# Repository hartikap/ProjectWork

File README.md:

# ProjectWork
Ohjelmistokehitys-koulutuksen projektityö

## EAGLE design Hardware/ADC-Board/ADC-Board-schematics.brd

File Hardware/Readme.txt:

This folder includes all hardware -schematics, layouts and BOMs for different modules of the synthesizer. 
VCO-1, VCA-1 and VCF-1 modules are (for the time being) constructed using the design and instructions 
found from http://www.birthofasynth.com/Thomas_Henry/TH_main.html. Other modules are designed by myself.

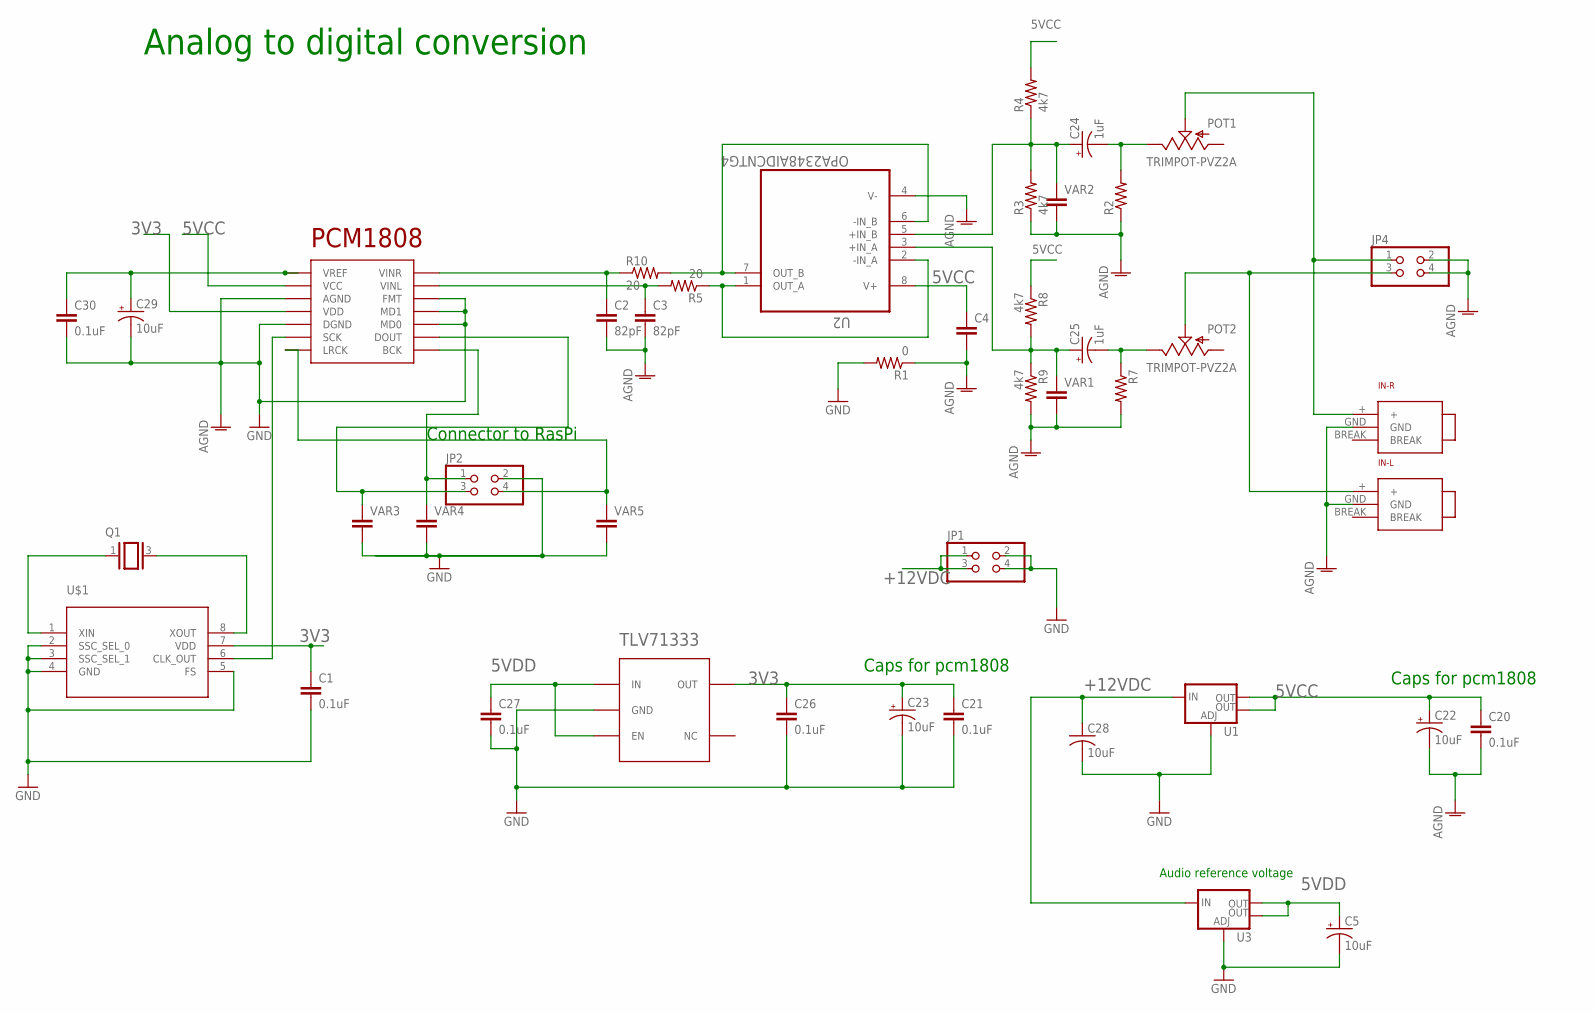
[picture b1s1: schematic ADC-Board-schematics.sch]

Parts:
C1, C20, C21, C26, C27, C30: 0.1uF; C0603
C2, C3: 82pF; 0603-CAP
C4: CAP0603-CAP; 0603-CAP
C5, C22, C23, C29: 10uF; RADIALCAN4MM
C24, C25: 1uF; RADIALCAN4MM
C28: 10uF; C1206
IN-L: 3MM5-PLUG
IN-R: 3MM5-PLUG
JP1, JP2, JP4: PINHD-2X2; 2X02
PCM1808: PCM1808PW; R-PDSO-G14
POT1, POT2: TRIMPOT-PVZ2A; PVZ2A
Q1: XTAL; 5X3CRYSTAL
R1: 0; 0603-RES
R2, R7: RESISTOR0603-RES; 0603-RES
R3, R4, R8, R9: 4k7; 0603-RES
R5, R10: 20; 0603-RES
TLV71333: TVL713; SOT23-5
U1, U3: V_REG_LM1117SOT223; SOT223
U2: OPA2348AIDCNTG4; SOT65P280X145-8N
U$1: CDCS502TSSOP-8; TSSOP-8
VAR1, VAR2, VAR3, VAR4, VAR5: CAP0603-CAP; 0603-CAP

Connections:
3V3: C1.1, C21.1, C23.1 (+), C26.1, PCM1808.4 (VDD), TLV71333.5 (OUT), U$1.7 (VDD)
5VCC: C4.1, C20.1, C22.1 (+), PCM1808.3 (VCC), R4.2, R8.1, U1.2 (OUT), U1.4 (OUT), U2.8 (V+)
5VDD: C5.1 (+), C27.1, TLV71333.1 (IN), TLV71333.3 (EN), U3.2 (OUT), U3.4 (OUT)
+12VDC: C28.1, JP1.1, JP1.3, U1.3 (IN), U3.3 (IN)
AGND: C2.2, C3.2, C4.2, IN-L.GND, IN-R.GND, JP4.2, JP4.4, R1.1, R2.1, R3.1, R7.2, R9.2, U2.4 (V-), VAR1.2, VAR2.2
GND: C1.2, C5.2 (-), C20.2, C21.2, C22.2 (-), C23.2 (-), C26.2, C27.2, C28.2, C29.2 (-), C30.2, JP1.2, JP1.4, JP2.2, PCM1808.2 (AGND), PCM1808.5 (DGND), PCM1808.10 (MD0), PCM1808.11 (MD1), PCM1808.12 (FMT), R1.2, TLV71333.2 (GND), U1.1 (ADJ), U3.1 (ADJ), U$1.2 (SSC_SEL_0), U$1.3 (SSC_SEL_1), U$1.4 (GND), U$1.5 (FS), VAR3.2, VAR4.2, VAR5.2
unnamed: JP2.1, PCM1808.8 (BCK), VAR4.1
unnamed: C24.2 (-), POT1.3 (E), R2.2
unnamed: JP2.3, PCM1808.9 (DOUT), VAR3.1
unnamed: C24.1 (+), R3.2, R4.1, U2.5 (+IN_B), VAR2.1
unnamed: R5.1, U2.1 (OUT_A), U2.2 (-IN_A)
unnamed: C3.1, PCM1808.13 (VINL), R5.2
unnamed: C25.2 (-), POT2.3 (E), R7.1
unnamed: C25.1 (+), R8.2, R9.1, U2.3 (+IN_A), VAR1.1
unnamed: R10.2, U2.6 (-IN_B), U2.7 (OUT_B)
unnamed: C2.1, PCM1808.14 (VINR), R10.1
unnamed: JP2.4, PCM1808.7 (LRCK), VAR5.1
unnamed: IN-L.+, JP4.3, POT2.2 (S)
unnamed: IN-R.+, JP4.1, POT1.2 (S)
unnamed: Q1.1, U$1.1 (XIN)
unnamed: Q1.3 (2), U$1.8 (XOUT)
unnamed: C29.1 (+), C30.1, PCM1808.1 (VREF)
unnamed: PCM1808.6 (SCK), U$1.6 (CLK_OUT)

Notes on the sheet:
Caps for pcm1808
Analog to digital conversion
Connector to RasPi
Audio reference voltage

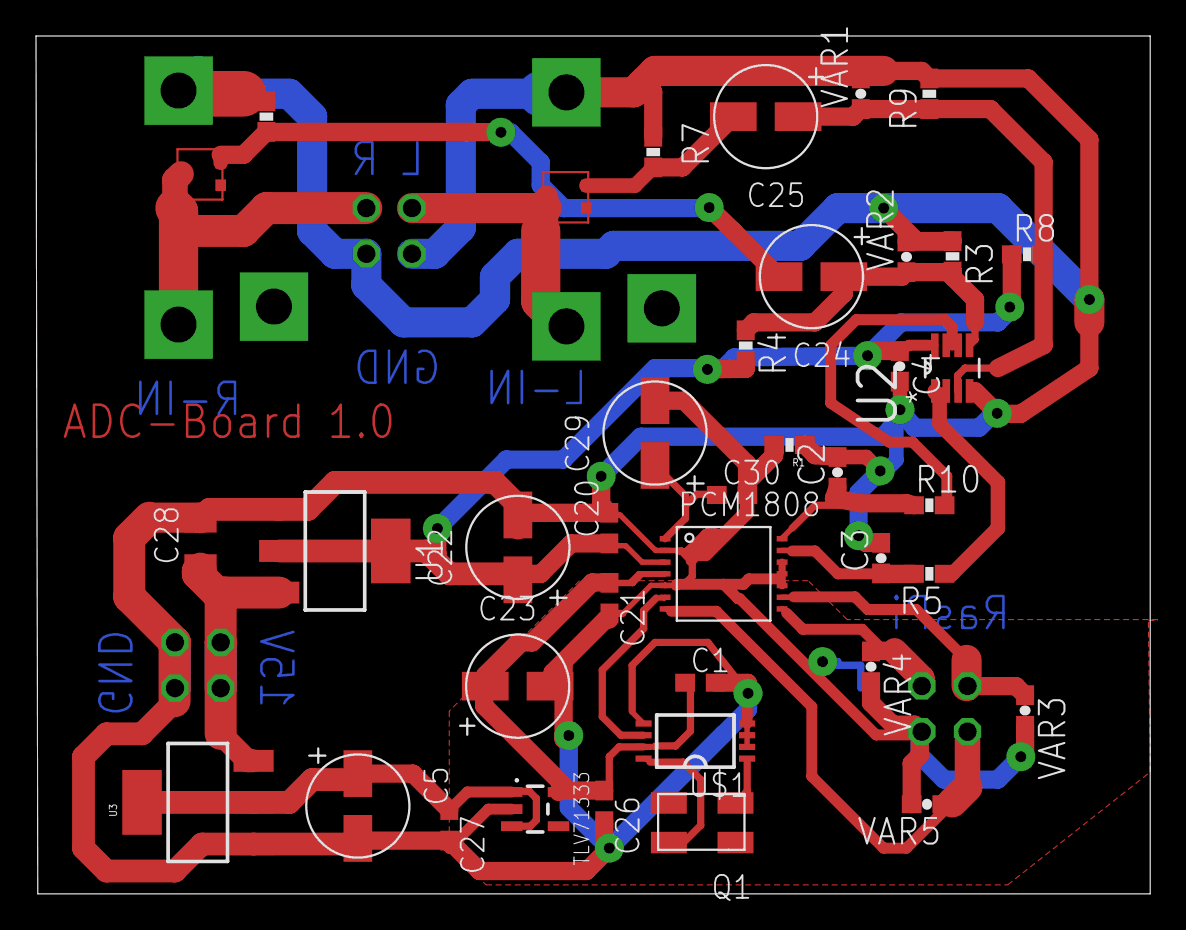
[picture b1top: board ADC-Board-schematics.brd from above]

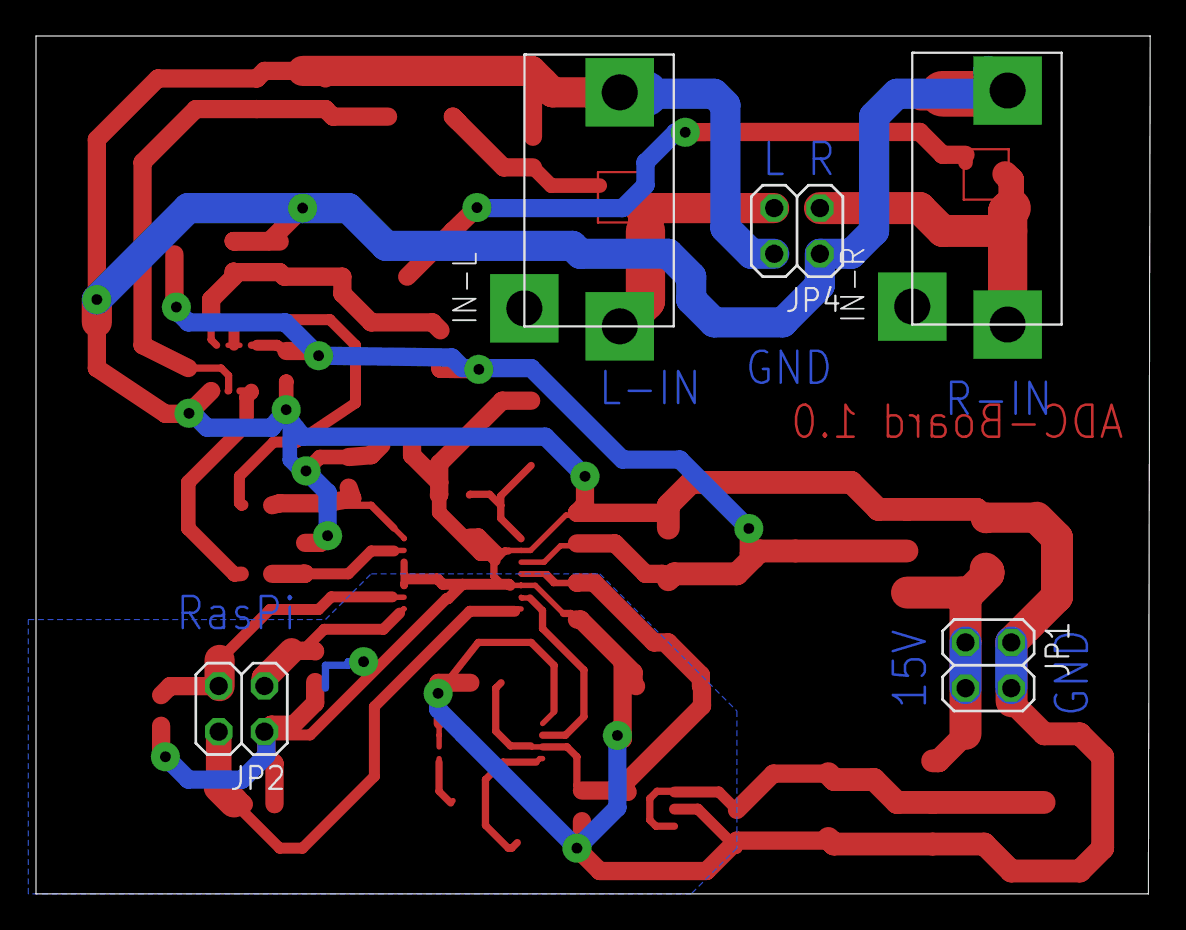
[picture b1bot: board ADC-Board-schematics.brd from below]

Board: 2 copper layers, 61.9 x 47.7 mm, 44 parts (5 on the bottom side), 23 nets.

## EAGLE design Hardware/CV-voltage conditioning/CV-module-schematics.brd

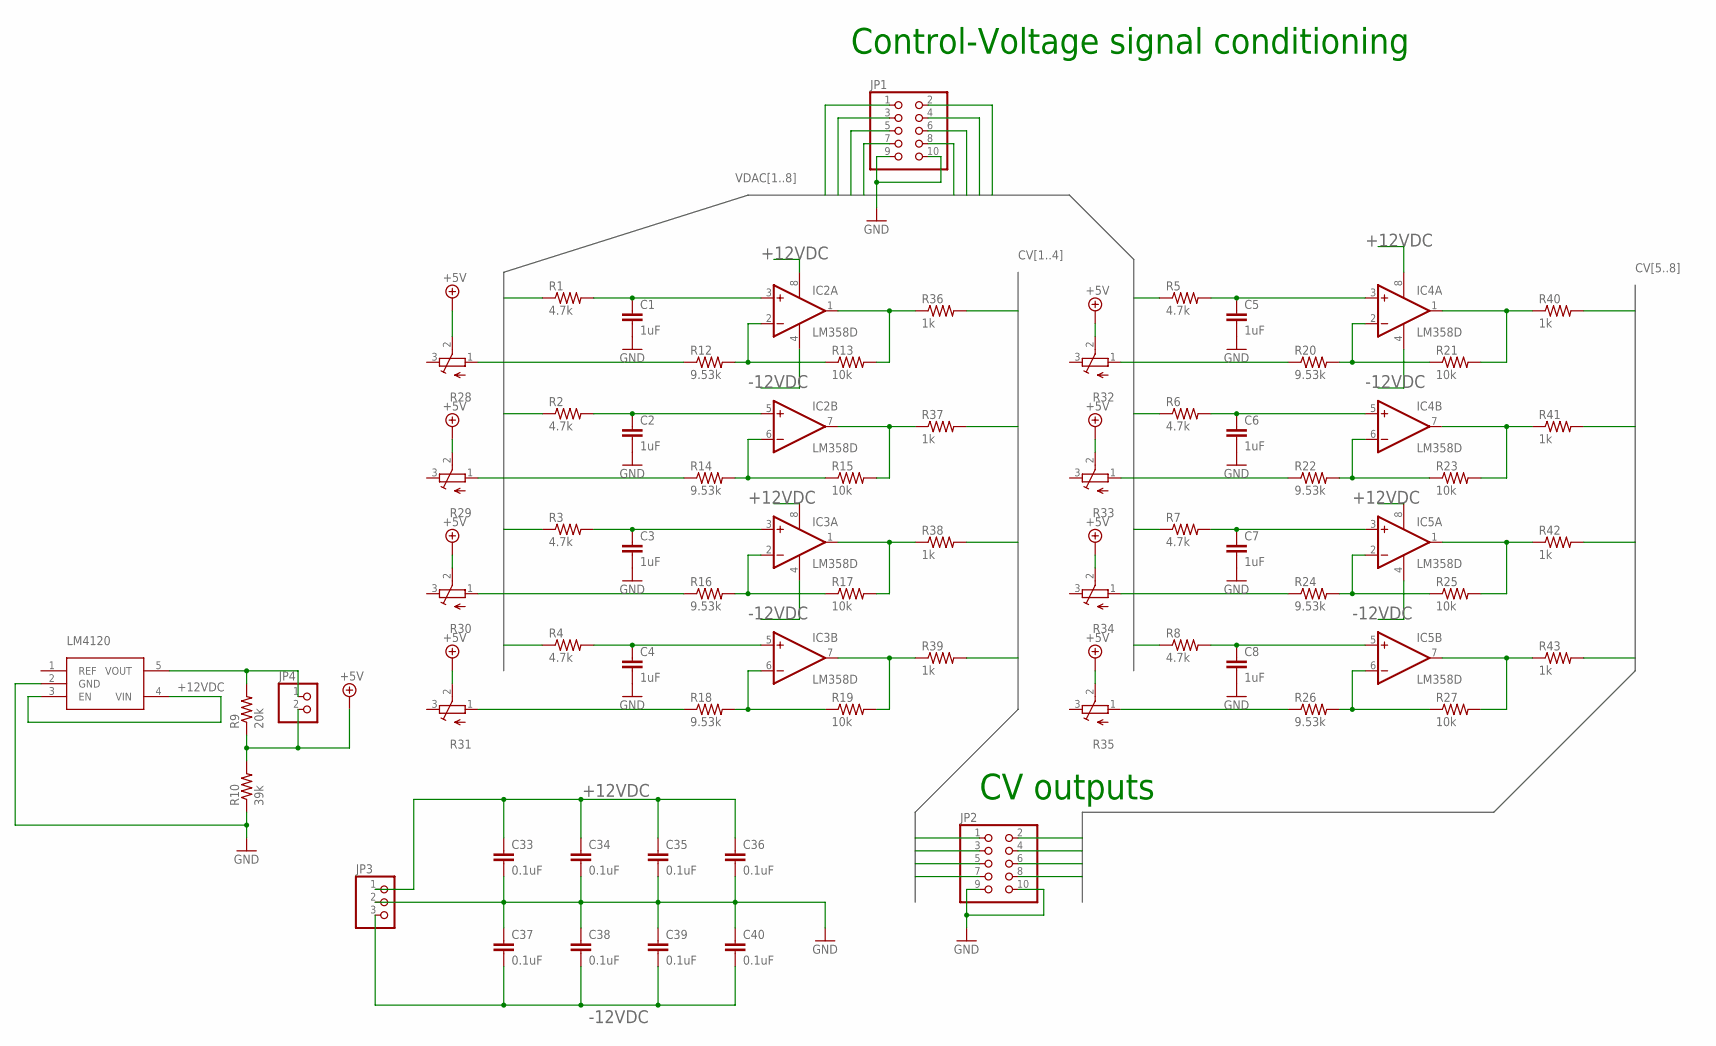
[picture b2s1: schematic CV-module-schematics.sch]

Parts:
C1, C2, C3, C4, C5, C6, C7, C8: 1uF; C0603
C33, C34, C35, C36, C37, C38, C39, C40: 0.1uF; C0603
IC2, IC3, IC4, IC5: LM358D; SO08
JP1, JP2: PINHD-2X5; 2X05
JP3: PINHD-1X3; 1X03
JP4: PINHD-1X2; 1X02
LM4120: LM4120; SOT23-5
R1, R2, R3, R4, R5, R6, R7, R8: 4.7k; R0603
R9: 20k; R0603
R10: 39k; R0603
R12, R14, R16, R18, R20, R22, R24, R26: 9.53k; R0603
R13, R15, R17, R19, R21, R23, R25, R27: 10k; R0603
R28, R29, R30, R31, R32, R33, R34, R35: TRIM_EU-3222W; 3222W
R36, R37, R38, R39, R40, R41, R42, R43: 1k; R0603

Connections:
+5V: JP4.2, R9.1, R10.2, R28.2 (S), R29.2 (S), R30.2 (S), R31.2 (S), R32.2 (S), R33.2 (S), R34.2 (S), R35.2 (S)
+12VDC: C33.1, C34.1, C35.1, C36.1, IC2.8 (V+), IC3.8 (V+), IC4.8 (V+), IC5.8 (V+), JP3.1, LM4120.3 (EN), LM4120.4 (VIN)
-12VDC: C37.2, C38.2, C39.2, C40.2, IC2.4 (V-), IC3.4 (V-), IC4.4 (V-), IC5.4 (V-), JP3.3
CV1: JP2.1, R37.2
CV2: JP2.3, R36.2
CV3: JP2.5, R39.2
CV4: JP2.7, R38.2
CV5: JP2.2, R42.2
CV6: JP2.4, R43.2
CV7: JP2.6, R40.2
CV8: JP2.8, R41.2
GND: C1.2, C2.2, C3.2, C4.2, C5.2, C6.2, C7.2, C8.2, C33.2, C34.2, C35.2, C36.2, C37.1, C38.1, C39.1, C40.1, JP1.9, JP1.10, JP2.9, JP2.10, JP3.2, LM4120.2 (GND), R10.1
unnamed: C1.1, IC2.3 (+IN), R1.2
unnamed: C2.1, IC2.5 (+IN), R2.2
unnamed: C3.1, IC3.3 (+IN), R3.2
unnamed: IC2.2 (-IN), R12.2, R13.1
unnamed: R12.1, R28.1 (A)
unnamed: IC2.1 (OUT), R13.2, R36.1
unnamed: R14.1, R29.1 (A)
unnamed: IC2.6 (-IN), R14.2, R15.1
unnamed: IC3.2 (-IN), R16.2, R17.1
unnamed: R16.1, R30.1 (A)
unnamed: IC3.6 (-IN), R18.2, R19.1
unnamed: R18.1, R31.1 (A)
unnamed: IC3.7 (OUT), R19.2, R39.1
unnamed: IC3.1 (OUT), R17.2, R38.1
unnamed: IC2.7 (OUT), R15.2, R37.1
unnamed: IC4.2 (-IN), R20.2, R21.1
unnamed: IC4.1 (OUT), R21.2, R40.1
unnamed: IC4.7 (OUT), R23.2, R41.1
unnamed: IC4.6 (-IN), R22.2, R23.1
unnamed: IC5.2 (-IN), R24.2, R25.1
unnamed: IC5.1 (OUT), R25.2, R42.1
unnamed: R24.1, R34.1 (A)
unnamed: IC5.6 (-IN), R26.2, R27.1
unnamed: IC5.7 (OUT), R27.2, R43.1
unnamed: R26.1, R35.1 (A)
unnamed: R20.1, R32.1 (A)
unnamed: R22.1, R33.1 (A)
unnamed: C4.1, IC3.5 (+IN), R4.2
unnamed: C5.1, IC4.3 (+IN), R5.2
unnamed: C6.1, IC4.5 (+IN), R6.2
unnamed: C7.1, IC5.3 (+IN), R7.2
unnamed: C8.1, IC5.5 (+IN), R8.2
unnamed: JP4.1, LM4120.5 (VOUT), R9.2
VDAC1: JP1.1, R1.1
VDAC2: JP1.2, R2.1
VDAC3: JP1.3, R3.1
VDAC4: JP1.4, R4.1
VDAC5: JP1.5, R5.1
VDAC6: JP1.6, R6.1
VDAC7: JP1.7, R7.1
VDAC8: JP1.8, R8.1

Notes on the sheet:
Control-Voltage signal conditioning
CV outputs

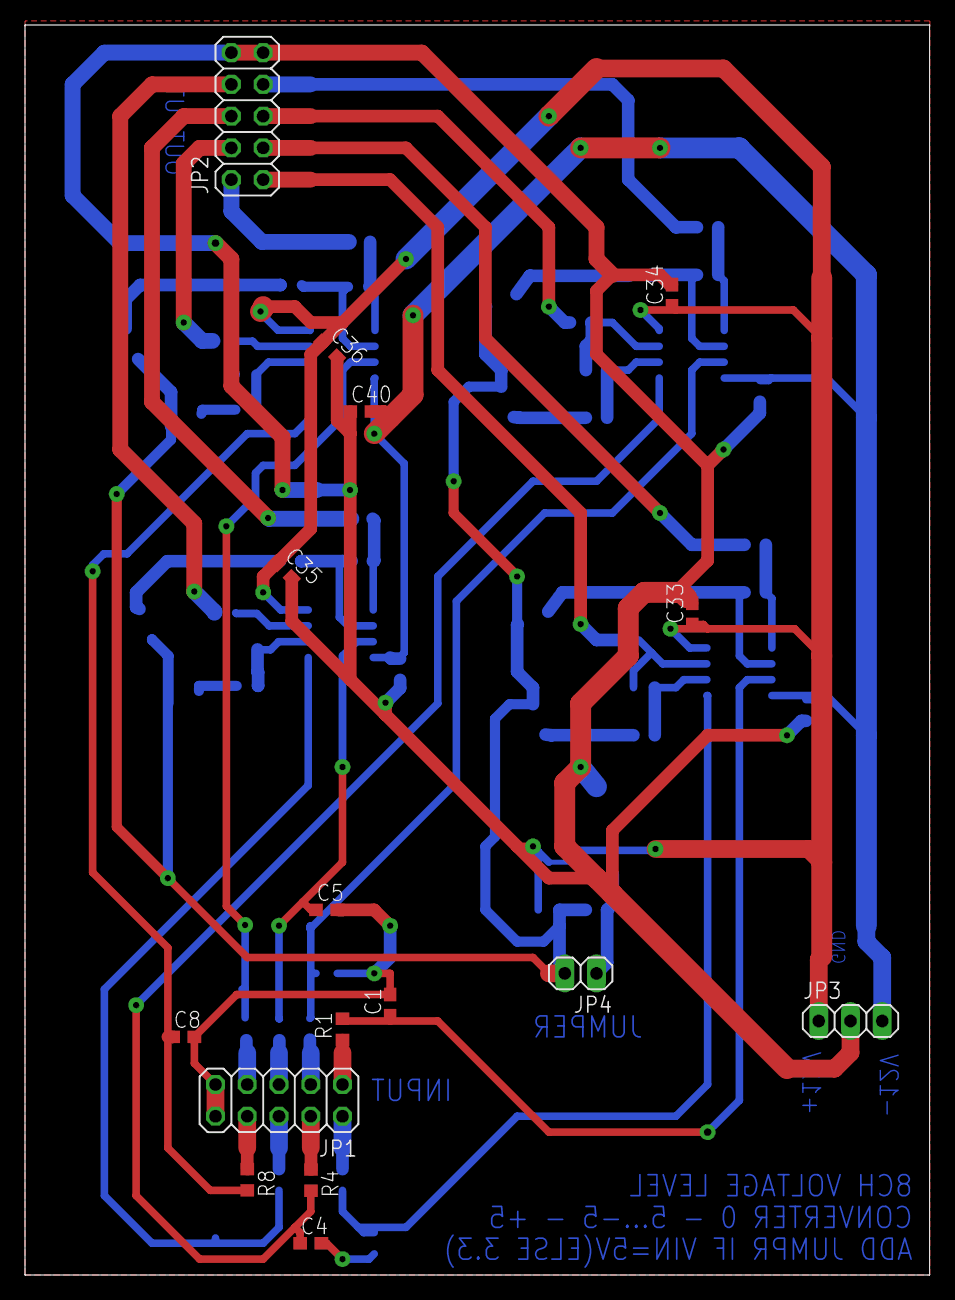
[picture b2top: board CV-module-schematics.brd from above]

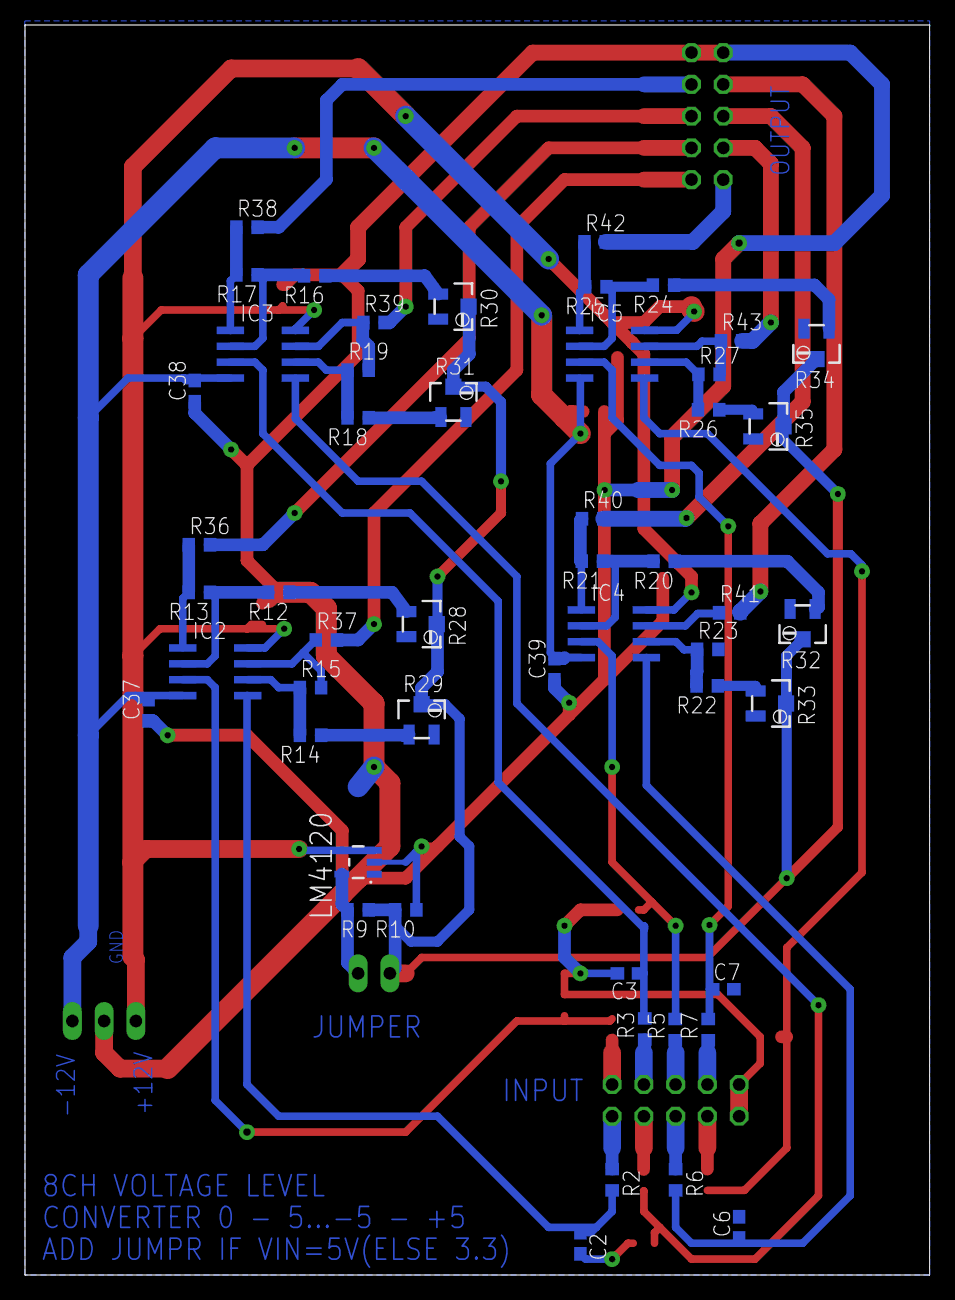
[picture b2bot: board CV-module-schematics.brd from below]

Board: 2 copper layers, 72.4 x 100.0 mm, 67 parts (51 on the bottom side), 53 nets.

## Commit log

2015-10-28 Lisäsin pari muistiinpanotiedostoa
2015-10-29 Added block diagram
2015-10-29 updated block diagram
2015-10-29 Link update
2015-10-29 Part-list and links added
2015-11-02 Partlist updated
2015-11-02 Added folders etc
2015-11-03 Added eagle project for CV-Module
2015-11-03 link added
2015-11-04 working on eagle-project
2015-11-11 HW-design phase
2015-11-11 eagle project forward
2015-11-12 HW schematics and layout +parts updated
2015-11-13 Schema and Layout
2015-11-16 layout forward
2015-11-17 Schema and layout design
2015-11-18 layout&schematics
2015-11-19 Schemas and layout updated
2015-11-24 Few links
2015-11-27 parts
2015-11-29 Front-end
2015-11-30 front-end developing
2015-12-06 front end and arduino code
2015-12-09 to angular
2015-12-16 arduino code update
2015-12-17 arduino code
2015-12-18 arduino code updated
2016-01-06 updates for voltage-level module
2016-01-14 Updates!
2016-01-15 layouts
2016-01-17 tvs considerations
2016-02-21 adc-board
2016-02-28 some hw changes
2016-03-09 Layout and parts
2016-03-10 ADC-board layout
2016-03-11 layout
2016-03-11 files
2016-04-17 linkkejä

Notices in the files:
parts and their libraries:
SparkFun-PowerIC: Licensing: Creative Commons ShareAlike 4.0 International - https://creativecommons.org/licenses/by-sa/4.0
